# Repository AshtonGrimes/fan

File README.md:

This repository includes the firmware and KiCAD schematic/PCB for my fan controller project.

The board uses USB-A for the 5 volt power supply, with header pins for the fan wiring and fan power supply.

The firmware is written for the ATMEGA328P in AVR assembly, currently providing a sequence of three states: off, 100% duty cycle, and 50% duty cycle. It also manages button debouncing and reduces the relay contact noise, which is otherwise quite loud on the relay used in the schematic. Using a relay in this application, despite MOSFETs being more appropriate in most situations, allows using any choice of power supply for the fan.

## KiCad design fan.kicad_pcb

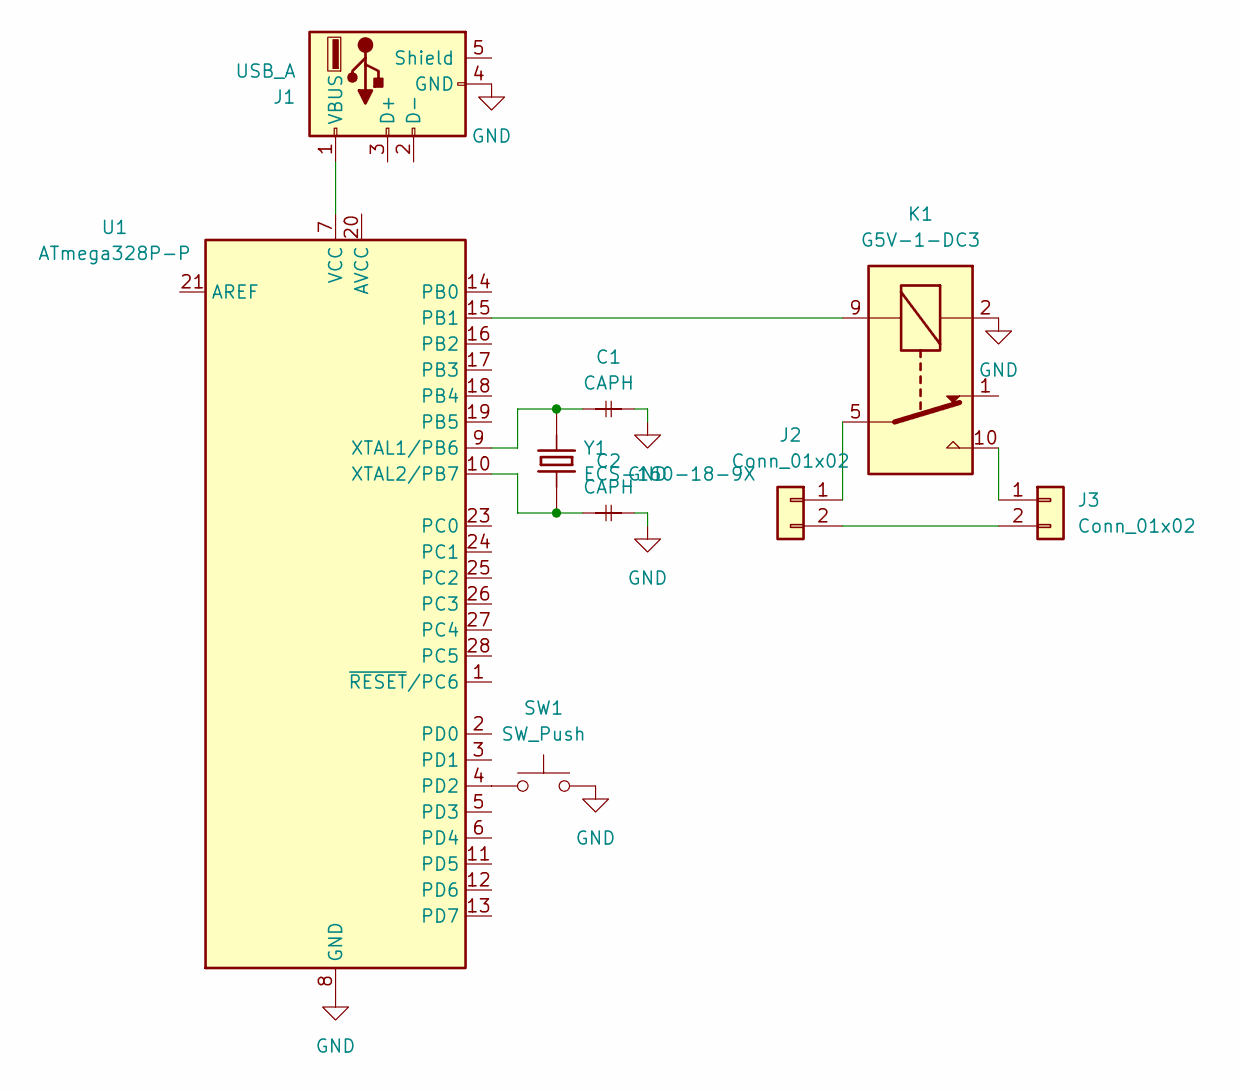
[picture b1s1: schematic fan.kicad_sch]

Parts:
C1, C2: CAPH; GRM1555C1H270JA01D
J1: USB_A; USB_A_CNCTech_1001-011-01101_Horizontal
J2, J3: Conn_01x02; PinSocket_1x02_P2.54mm_Vertical
K1: G5V-1-DC3; Relay_SPDT_Omron_G5V-1
SW1: SW_Push; SW_PUSH_6mm_H5mm
U1: ATmega328P-P; DIP-28_W7.62mm
Y1: ECS-160-18-9X; XTAL_ECS-160-18-9X

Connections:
GND: C1.2, C2.2, J1.4 (GND), K1.2, SW1.2, U1.8 (GND), U1.22 (GND)
unnamed: J1.1 (VBUS), U1.7 (VCC)
unnamed: J2.1, K1.5, K1.6
unnamed: J2.2, J3.2
unnamed: J3.1, K1.10
unnamed: K1.9, U1.15 (PB1)
unnamed: SW1.1, U1.4 (PD2)
unnamed: C1.1, U1.9 (XTAL1/PB6), Y1.2
unnamed: C2.1, U1.10 (XTAL2/PB7), Y1.1

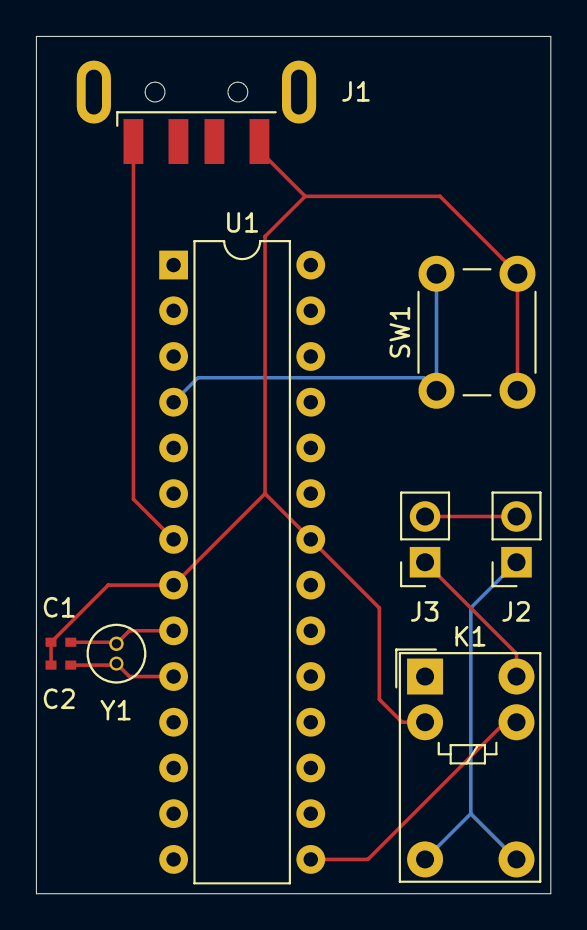
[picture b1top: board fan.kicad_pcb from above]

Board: 2 copper layers, 28.6 x 47.6 mm, 9 parts (0 on the bottom side), 9 nets.

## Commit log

2024-11-24 Add project files
